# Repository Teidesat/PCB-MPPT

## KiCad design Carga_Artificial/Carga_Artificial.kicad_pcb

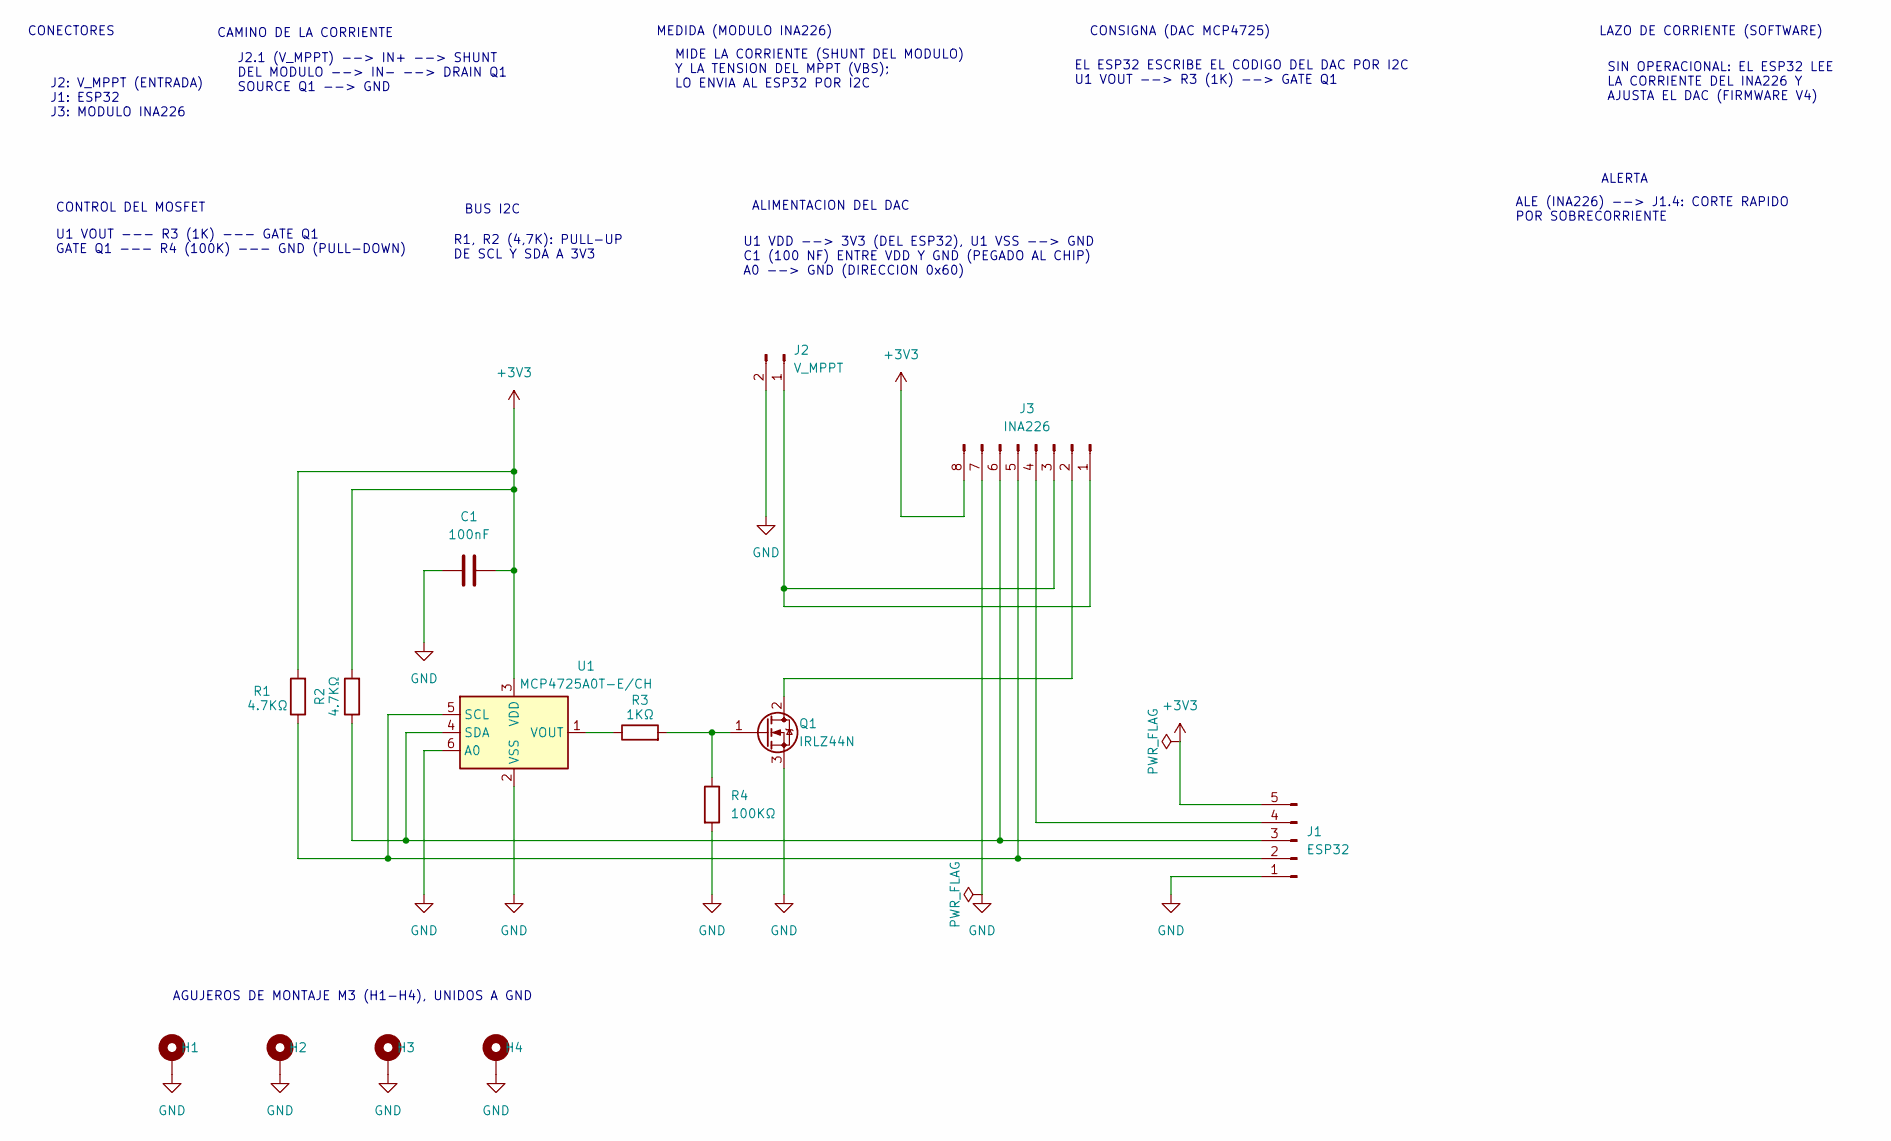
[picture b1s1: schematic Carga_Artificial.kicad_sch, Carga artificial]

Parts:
C1: 100nF; C_0805_2012Metric; MPN CC0805KRX7R9BB104; Mouser 603-CC805KRX7R9BB104
H1, H2, H3, H4: MountingHole_Pad; MountingHole_3.2mm_M3_Pad_Via
J1: ESP32; PinSocket_1x05_P2.54mm_Vertical; MPN 61300511121; Mouser 710-61300511121
J2: V_MPPT; PinSocket_1x02_P2.54mm_Vertical; MPN 61300211121; Mouser 710-61300211121
J3: INA226; PinSocket_1x08_P2.54mm_Vertical; MPN 61300811121; Mouser 710-61300811121
Q1: IRLZ44N; TO-220-3_Vertical; MPN IRLZ44NPBF; Mouser 942-IRLZ44NPBF
R1, R2: 4.7KΩ; R_0805_2012Metric; MPN RC0805FR-074K7L; Mouser 603-RC0805FR-074K7L
R3: 1KΩ; R_0805_2012Metric; MPN RC0805FR-071KL; Mouser 603-RC0805FR-071KL
R4: 100KΩ; R_0805_2012Metric; MPN RC0805FR-07100KL; Mouser 603-RC0805FR-07100KL
U1: MCP4725A0T-E/CH; SOT-23-6; MPN MCP4725A0T-E/CH; Mouser 579-MCP4725A0TECH

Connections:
+3V3: C1.2, J1.5, J3.8, R1.2, R2.2, U1.3 (VDD)
GND: C1.1, H1.1, H2.1, H3.1, H4.1, J1.1, J2.2, J3.7, Q1.3 (S), R4.2, U1.2 (VSS), U1.6 (A0)
unnamed: J1.2, J3.5, R1.1, U1.5 (SCL)
unnamed: J1.3, J3.6, R2.1, U1.4 (SDA)
unnamed: J1.4, J3.4
unnamed: J2.1, J3.1, J3.3
unnamed: J3.2, Q1.2 (D)
unnamed: Q1.1 (G), R3.2, R4.1
unnamed: R3.1, U1.1 (VOUT)

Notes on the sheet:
BUS I2C
SIN OPERACIONAL: EL ESP32 LEE LA CORRIENTE DEL INA226 Y AJUSTA EL DAC (FIRMWARE V4)
LAZO DE CORRIENTE (SOFTWARE)
R1, R2 (4,7K): PULL-UP DE SCL Y SDA A 3V3
J2: V_MPPT (ENTRADA) J1: ESP32 J3: MODULO INA226
MIDE LA CORRIENTE (SHUNT DEL MODULO) Y LA TENSION DEL MPPT (VBS); LO ENVIA AL ESP32 POR I2C
CONECTORES
ALE (INA226) --> J1.4: CORTE RAPIDO POR SOBRECORRIENTE
EL ESP32 ESCRIBE EL CODIGO DEL DAC POR I2C U1 VOUT --> R3 (1K) --> GATE Q1
ALERTA
J2.1 (V_MPPT) --> IN+ --> SHUNT DEL MODULO --> IN- --> DRAIN Q1 SOURCE Q1 --> GND
ALIMENTACION DEL DAC
CAMINO DE LA CORRIENTE
MEDIDA (MODULO INA226)
CONSIGNA (DAC MCP4725)
U1 VOUT --- R3 (1K) --- GATE Q1 GATE Q1 --- R4 (100K) --- GND (PULL-DOWN)
U1 VDD --> 3V3 (DEL ESP32), U1 VSS --> GND C1 (100 NF) ENTRE VDD Y GND (PEGADO AL CHIP) A0 --> GND (DIRECCION 0x60)
CONTROL DEL MOSFET
AGUJEROS DE MONTAJE M3 (H1-H4), UNIDOS A GND

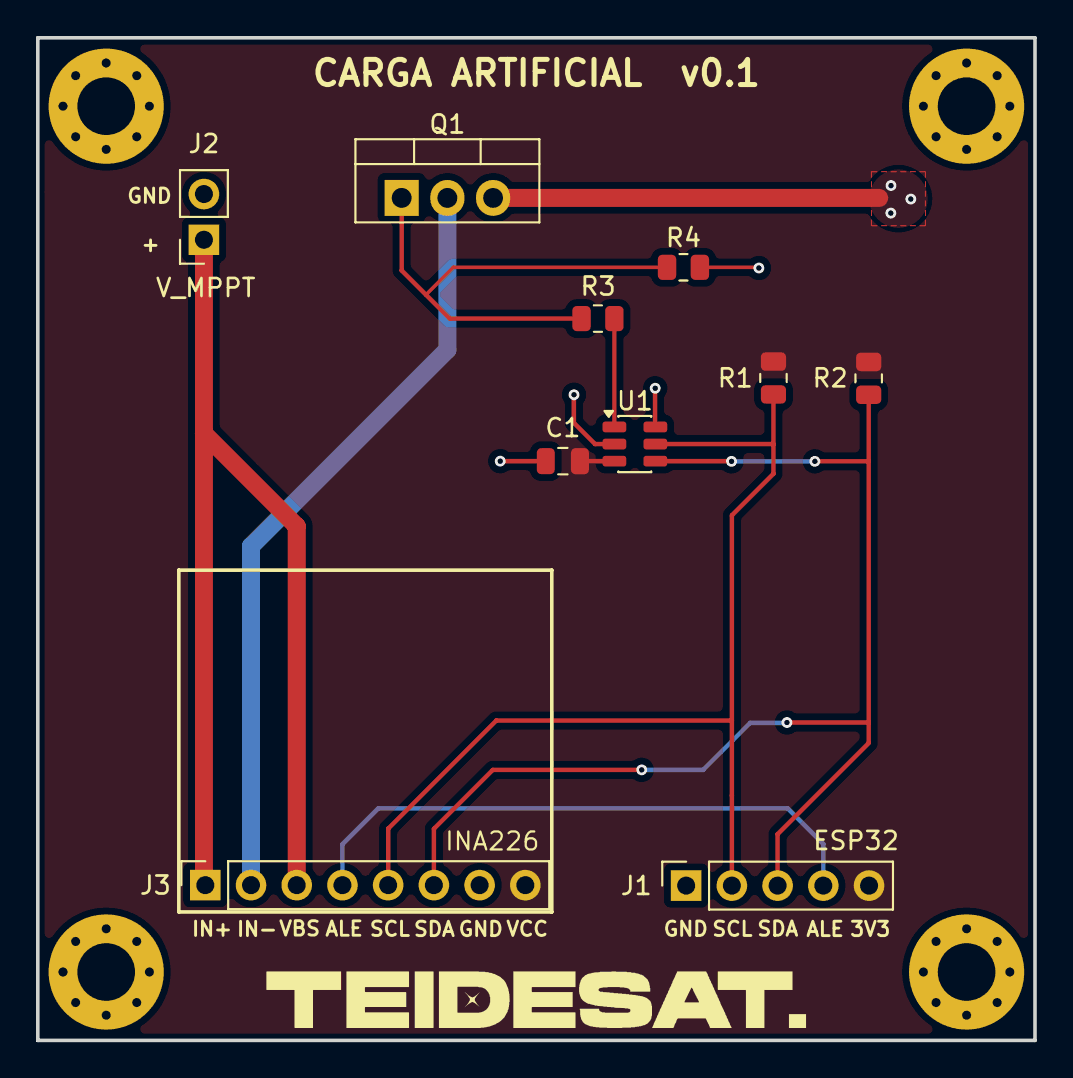
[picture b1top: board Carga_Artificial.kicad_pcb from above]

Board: 2 copper layers, 55.4 x 55.7 mm, 14 parts (0 on the bottom side), 9 nets.
